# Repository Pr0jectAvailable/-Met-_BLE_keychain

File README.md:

# -Met-_BLE_keychain
"Met"_BLE_keychain is a device that operates using BLE technology. It broadcasts data about itself and listens for similar devices.

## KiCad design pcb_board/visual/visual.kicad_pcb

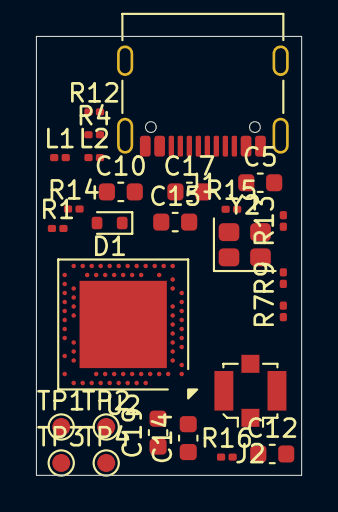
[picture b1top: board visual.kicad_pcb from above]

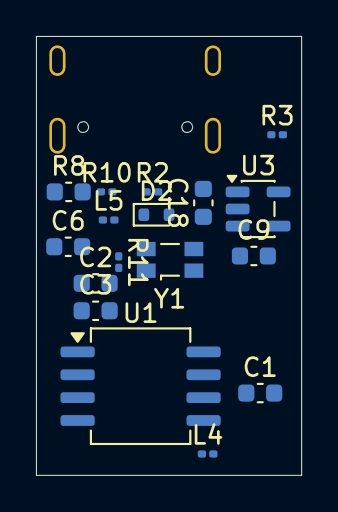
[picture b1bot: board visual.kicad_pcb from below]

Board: 2 copper layers, 14.7 x 24.4 mm, 44 parts (17 on the bottom side), 5 nets, no tracks yet.

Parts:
C1, C2, C3, C5, C6, C9, C10, C12, C14, C15, C17, C18, C19: C; C_0603_1608Metric
D1, D2: 1N914WT; D_SOD-523
J1: USB_C_Receptacle_USB2.0_14P; USB_C_Receptacle_Palconn_UTC16-G
J2: Conn_Coaxial_Small; U.FL_Molex_MCRF_73412-0110_Vertical
L1, L2: L; C_0201_0603Metric
L4, L5: L_Small; C_0201_0603Metric
R1, R2, R3, R4, R7, R9, R10, R11, R12, R13, R14, R15, R16: R; C_0201_0603Metric
R8: R; C_0603_1608Metric
TP1, TP2, TP3, TP4: TestPoint; TestPoint_Pad_D1.0mm
U1: MB85RS2MTAPNF; SOIC-8_5.3x6.2mm_P1.27mm
U2: nRF52840; Nordic_AQFN-73-1EP_7x7mm_P0.5mm
U3: MCP73831-3-OT; SOT-23-5
Y1: SG-3030CM; Oscillator_SMD_SeikoEpson_SG3030CM
Y2: Crystal_GND24_Small; Crystal_SMD_2520-4Pin_2.5x2.0mm

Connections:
unnamed: J1.A1 (GND), J1.A12 (GND), J1.B1 (GND), J1.B12 (GND)
unnamed: J1.A4 (VBUS), J1.A9 (VBUS), J1.B4 (VBUS), J1.B9 (VBUS)
unnamed: U2.A22 (VDD), U2.AD14 (VDD), U2.AD23 (VDD), U2.B1 (VDD), U2.W1 (VDD)
unnamed: U2.B7 (VSS), U2.EP (VSS)
unnamed: Y2.2 (G), Y2.4 (G)
